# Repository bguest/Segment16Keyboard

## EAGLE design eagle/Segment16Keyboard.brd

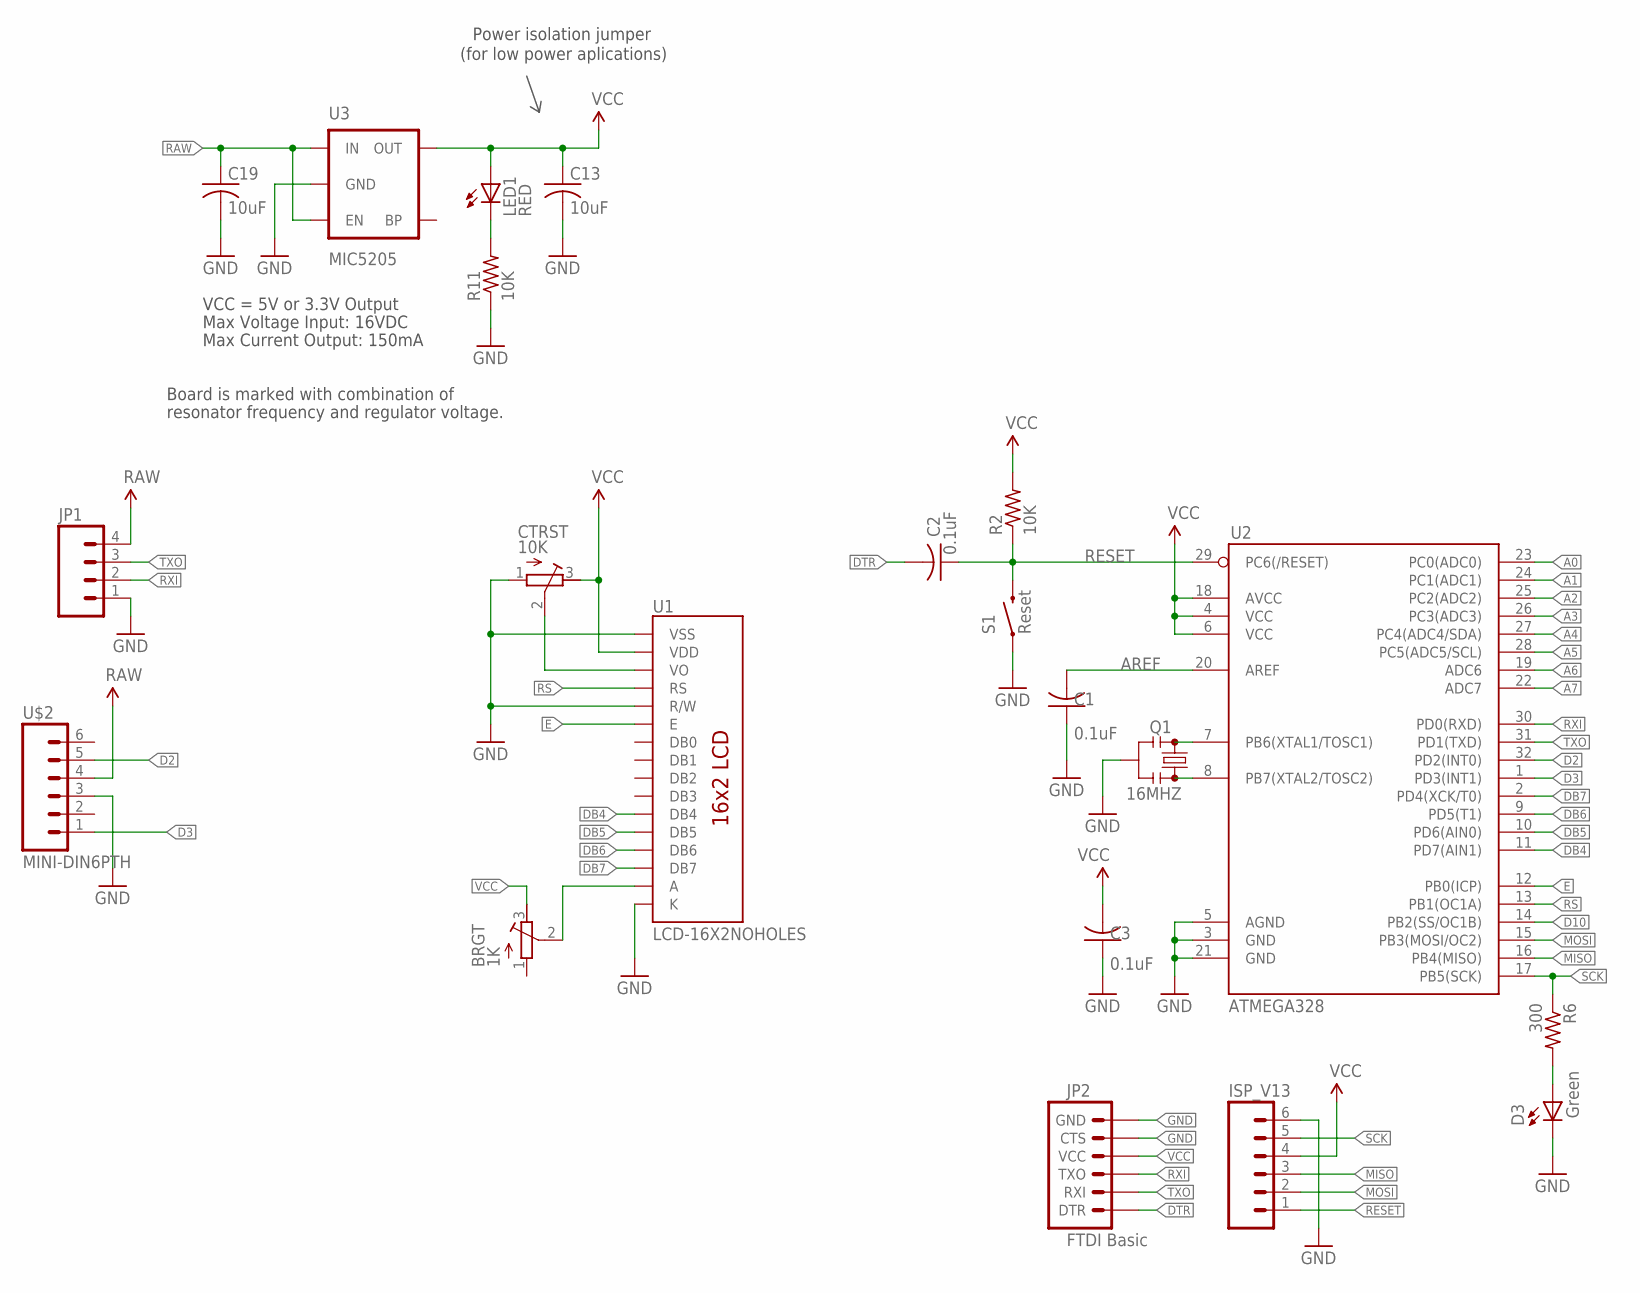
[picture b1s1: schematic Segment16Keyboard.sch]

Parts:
BRGT: 1K; RTRIM3296W
C1, C2, C3: 0.1uF; C0805
C13, C19: 10uF; C0805
CTRST: 10K; RTRIM3296W
D3: Green; CHIPLED_0805
ISP_V13: M06SIP; 1X06
JP1: M041X04_NO_SILK; 1X04_NO_SILK
JP2: FTDI Basic; 1X06
LED1: RED; 0603-LED-ALT1
Q1: 16MHZ; RESONATOR-SMD
R2: 10K; M0805
R6: 300; M0805
R11: 10K; R0805
S1: Reset; TACTILE-SWITCH-SMD-ALT01
U1: LCD-16X2NOHOLES; LCD-16X2_NOHOLES
U2: ATMEGA328; TQFP32-08
U3: MIC5205; SOT23-5
U$2: MINI-DIN6PTH; MINI-DIN6

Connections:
A: BRGT.2 (S), U1.15 (A)
A0: U2.23 (PC0(ADC0))
A1: U2.24 (PC1(ADC1))
A2: U2.25 (PC2(ADC2))
A3: U2.26 (PC3(ADC3))
A4: U2.27 (PC4(ADC4/SDA))
A5: U2.28 (PC5(ADC5/SCL))
A6: U2.19 (ADC6)
A7: U2.22 (ADC7)
AREF: C1.2, U2.20 (AREF)
D2: U2.32 (PD2(INT0)), U$2.5
D3: U2.1 (PD3(INT1)), U$2.1
D10: U2.14 (PB2(SS/OC1B))
DB4: U1.11 (DB4), U2.11 (PD7(AIN1))
DB5: U1.12 (DB5), U2.10 (PD6(AIN0))
DB6: U1.13 (DB6), U2.9 (PD5(T1))
DB7: U1.14 (DB7), U2.2 (PD4(XCK/T0))
DTR: C2.2, JP2.1 (DTR)
E: U1.6 (E), U2.12 (PB0(ICP))
GND: C1.1, C3.1, C13.2, C19.2, CTRST.1 (A), D3.C, ISP_V13.6, JP1.1, JP2.5 (CTS), JP2.6 (GND), Q1.2, R11.1, S1.1, S1.2 (1), U1.1 (VSS), U1.5 (R/W), U1.16 (K), U2.3 (GND), U2.5 (AGND), U2.21 (GND), U3.2 (GND), U$2.3
MISO: ISP_V13.3, U2.16 (PB4(MISO))
MOSI: ISP_V13.2, U2.15 (PB3(MOSI/OC2))
unnamed: D3.A, R6.2
unnamed: Q1.3, U2.8 (PB7(XTAL2/TOSC2))
unnamed: Q1.1, U2.7 (PB6(XTAL1/TOSC1))
unnamed: LED1.C, R11.2
RAW: C19.1, JP1.4, U3.1 (IN), U3.3 (EN), U$2.4
RESET: C2.1, ISP_V13.1, R2.1, S1.3 (2), S1.4 (2), U2.29 (PC6(/RESET))
RS: U1.4 (RS), U2.13 (PB1(OC1A))
RXI: JP1.2, JP2.3 (TXO), U2.30 (PD0(RXD))
SCK: ISP_V13.5, R6.1, U2.17 (PB5(SCK))
TXO: JP1.3, JP2.2 (RXI), U2.31 (PD1(TXD))
VCC: BRGT.3 (E), C3.2, C13.1, CTRST.3 (E), ISP_V13.4, JP2.4 (VCC), LED1.A, R2.2, U1.2 (VDD), U2.4 (VCC), U2.6 (VCC), U2.18 (AVCC), U3.5 (OUT)
VO: CTRST.2 (S), U1.3 (VO)

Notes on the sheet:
Max Voltage Input: 16VDC
Max Current Output: 150mA
Board is marked with combination of
resonator frequency and regulator voltage.
VCC = 5V or 3.3V Output
Power isolation jumper
(for low power aplications)

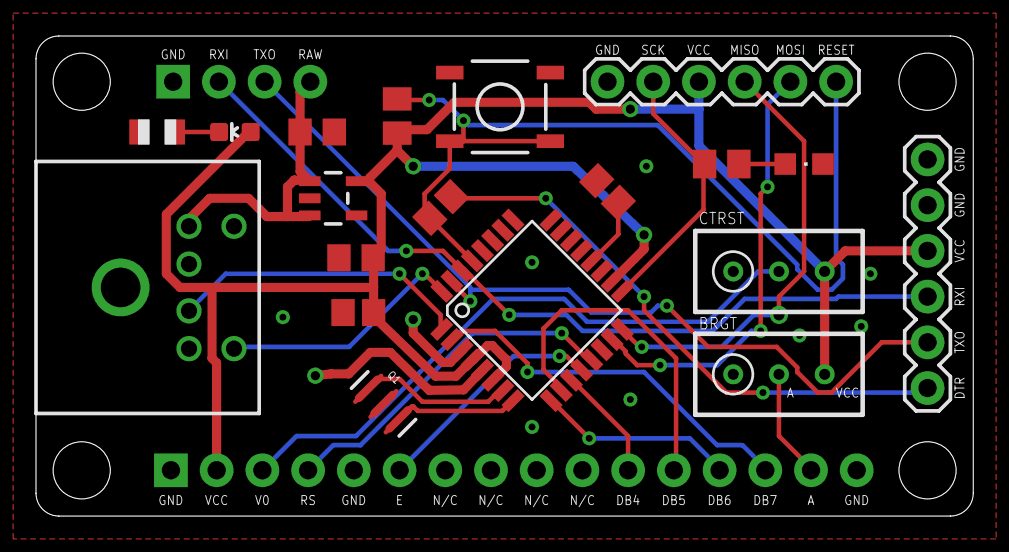
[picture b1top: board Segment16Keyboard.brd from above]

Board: 2 copper layers, 52.1 x 26.7 mm, 21 parts (0 on the bottom side), 25 nets.

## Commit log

2015-06-11 Make compatiable with both usb keybaord and serial
2015-06-28 Step towards remote keyboard
2015-06-28 Move Pins
2015-07-01 Make dumb terminal
2015-10-03 Switch pins to board layout
2016-07-14 Add V0 Board
2016-07-16 Board V1
2016-07-26 Increase via stop limit so they dont get masked
2016-08-06 Fix Pins for Real

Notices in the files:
parts and their libraries:
SparkFun-Connectors: Licensing: Creative Commons ShareAlike 4.0 International - https://creativecommons.org/licenses/by-sa/4.0
